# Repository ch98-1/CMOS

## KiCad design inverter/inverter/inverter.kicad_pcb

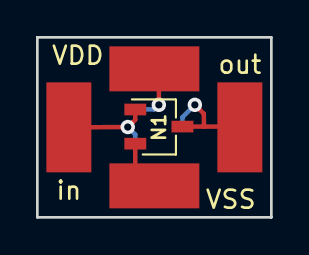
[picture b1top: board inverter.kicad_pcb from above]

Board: 2 copper layers, 13.0 x 10.0 mm, 6 parts (1 on the bottom side), 4 nets.

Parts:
J1: in; SolderWirePad_single_SMD_5x10mm
J2: VDD; SolderWirePad_single_SMD_5x10mm
J3: VSS; SolderWirePad_single_SMD_5x10mm
J4: out; SolderWirePad_single_SMD_5x10mm
N1: N; TSOT-23
P1: P; TSOT-23

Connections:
/Inv_1/in: J1.1, N1.1, P1.1
/Inv_1/out: J4.1, N1.3, P1.3
VDD: J2.1, P1.2
VSS: J3.1, N1.2

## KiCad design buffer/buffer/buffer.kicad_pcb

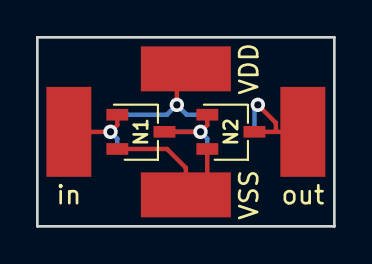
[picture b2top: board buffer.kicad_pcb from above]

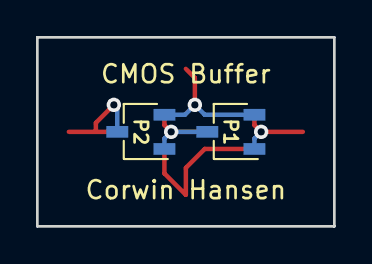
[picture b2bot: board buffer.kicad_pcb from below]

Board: 2 copper layers, 16.5 x 10.5 mm, 8 parts (2 on the bottom side), 5 nets.

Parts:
J1: in; SolderWirePad_single_SMD_5x10mm
J2: VDD; SolderWirePad_single_SMD_5x10mm
J3: VSS; SolderWirePad_single_SMD_5x10mm
J4: out; SolderWirePad_single_SMD_5x10mm
N1, N2: N; TSOT-23
P1, P2: P; TSOT-23

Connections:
/Buffer_1/Inv_2/in: N1.3, N2.1, P1.3, P2.1
/Buffer_1/in: J1.1, N1.1, P1.1
/Buffer_1/out: J4.1, N2.3, P2.3
VDD: J2.1, P1.2, P2.2
VSS: J3.1, N1.2, N2.2

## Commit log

2018-05-08 Changed license
2018-05-08 Modified the license to be for hardware too.
2018-05-08 Created buffer and updated file organisation
2018-05-15 Fixed a broken circuit
